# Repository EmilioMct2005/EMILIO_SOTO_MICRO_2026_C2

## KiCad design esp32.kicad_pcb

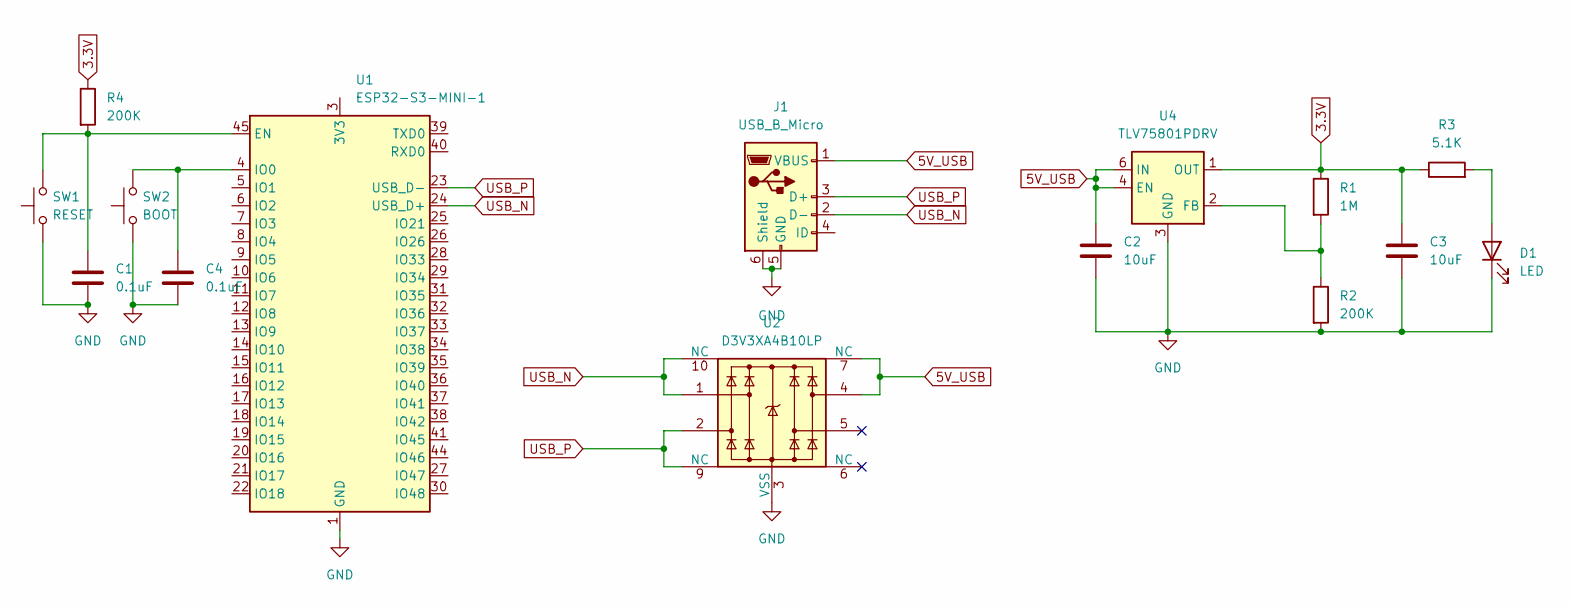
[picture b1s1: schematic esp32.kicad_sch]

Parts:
C1, C4: 0.1uF; C_0504_1310Metric
C2, C3: 10uF; C_0504_1310Metric
D1: LED; LED_miniPLCC_2315
J1: USB_B_Micro; USB_Micro-AB_Molex_47590-0001
R1: 1M; R_0402_1005Metric
R2, R4: 200K; R_0402_1005Metric
R3: 5.1K; R_0402_1005Metric
SW1: RESET; SW_Push_1P1T_NO_CK_KMR2
SW2: BOOT; SW_Push_1P1T_NO_CK_KMR2
U1: ESP32-S3-MINI-1; ESP32-S2-MINI-1
U2: D3V3XA4B10LP; Diodes_UDFN-10_1x2.5mm_P0.5mm
U4: TLV75801PDRV; WSON-6-1EP_2x2mm_P0.65mm_EP1x1.6mm

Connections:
3.3V: C3.1, R1.1, R3.1, R4.1, U4.1 (OUT)
5V_USB: C2.1, J1.1 (VBUS), U2.4, U2.7 (NC), U4.4 (EN), U4.6 (IN)
GND: C1.2, C2.2, C3.2, C4.2, D1.1 (K), J1.5 (GND), J1.6 (Shield), R2.2, SW1.1, SW2.1, U1.1 (GND), U1.2 (GND), U1.42 (GND), U1.43 (GND), U1.46 (GND), U1.47 (GND), U1.48 (GND), U1.49 (GND), U1.50 (GND), U1.51 (GND), U1.52 (GND), U1.53 (GND), U1.54 (GND), U1.55 (GND), U1.56 (GND), U1.57 (GND), U1.58 (GND), U1.59 (GND), U1.60 (GND), U1.61 (GND), U1.62 (GND), U1.63 (GND), U1.64 (GND), U1.65 (GND), U2.3 (VSS), U2.8 (VSS), U4.3 (GND), U4.7 (GND)
unnamed: D1.2 (A), R3.2
unnamed: C1.1, R4.2, SW1.2, U1.45 (EN)
unnamed: C4.1, SW2.2, U1.4 (IO0)
unnamed: R1.2, R2.1, U4.2 (FB)
USB_N: J1.2 (D-), U1.24 (USB_D+), U2.1, U2.10 (NC)
USB_P: J1.3 (D+), U1.23 (USB_D-), U2.2, U2.9 (NC)

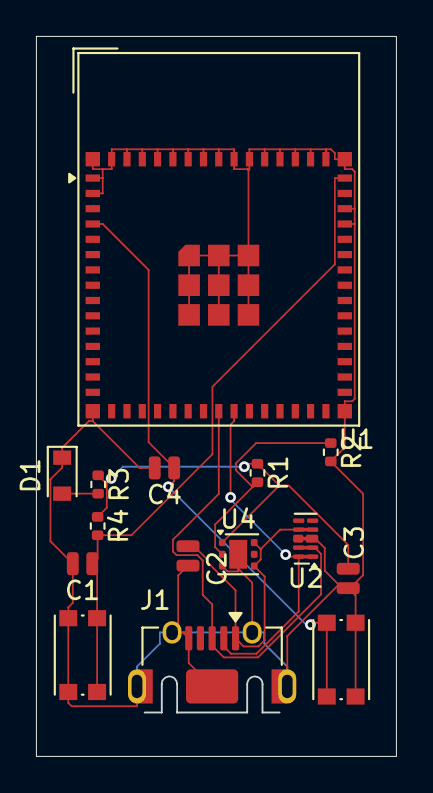
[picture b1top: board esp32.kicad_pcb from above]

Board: 2 copper layers, 20.0 x 40.0 mm, 15 parts (0 on the bottom side), 9 nets.
